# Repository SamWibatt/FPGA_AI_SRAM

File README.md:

# FPGA_AI_SRAM
Preliminary part of AI acceleration with FPGAs, interfacing external memory for greater capacity.

Memory chips I will use for the experiments are the [Cypress Semiconductor Corp. CY62157EV30LL-45ZXIT 1Mx8 SRAM (pdf)](https://www.cypress.com/file/43021/download) and the [Cypress Semiconductor Corp S29AL008J55TFNR10 1Mx8 Flash (pdf)](https://www.cypress.com/file/216396/download). 

Chose these for cost and simplicity. They have the same footprint. The Flash has the advantages of costing $0.60 in 10-quantity from Digi-Key, so being good for TSOP soldering practice, as well as being able to retain data while unpowered. The SRAM is pricier at $2.93 in single quantity, so not bad. (On edit: that's a fluke, because the chips don't have a warranty... do they work? I don't know. I just ordered 10 more in hopes that they do. I reckon sooner or later I will just need to use DRAM. **FOR LATER REFERENCE WRT DRAM** [Lattice has a project related to it](http://www.latticesemi.com/en/Products/DesignSoftwareAndIP/IntellectualProperty/ReferenceDesigns/ReferenceDesigns01/FastPageModeDRAMController) though that appears to be just with one kind. Find docs about it in general; writing an sdram controller might not be so scary and looks like a good intermediate project. Perhaps https://pdfs.semanticscholar.org/d960/f5cc9782719dcfa780b4f4aea51b8f791c62.pdf, and let's move this discussion to a new project or at least the wiki.)

Their interface is easy to understand and they're kind of OK for speed. Speed in actual wall time is not the point of this exercise so much as speed in terms of clock cycles; I'm looking more for savings of complexity which will translated to savings in time once it can run on "real" hardware.

# Objective

The initial goal is to try accelerating some data structures such as red/black trees and running some old AI techniques like A* to get a feel for how well programmable logic can tighten them up.

Ultimately, I want to implement modern methods such as RNNs, but since I'm still working on tiny cheap eval boards it's unlikely I can do much - but I will look into it, and I will learn some useful things in this endeavor that will transfer (transfer learning LOL) I imagine I'm also going to have to pick up DSP for best results there.

OK so now got this project cloned onto makevm4, let's try a push from it. Not on the VPN, so I expect it to work.

Copied over some initial stuff like osresearch's makefile for their serial project, need hack up to do what I want AND DO WHATEVER I NEED TO DO TO SATISFY THE TERMS OF THEIR LICENSE!!!!!!!!!!!!

# Notes

**Release / tag v0.1 should be a good skeleton for future icestorm projects** But [the repository VerilogSkeleton](https://github.com/SamWibatt/VerilogSkeleton) should also be that and I will maintain it as such.

I will be keeping my usual stream of consciousness [notes in the repo wiki, qv](https://github.com/SamWibatt/FPGA_AI_SRAM/wiki).

Makefile, Makefile.icestorm, and upduino_v2.pcf are copied and modified from osresearch's code at https://github.com/osresearch/up5k licensed under GPL3

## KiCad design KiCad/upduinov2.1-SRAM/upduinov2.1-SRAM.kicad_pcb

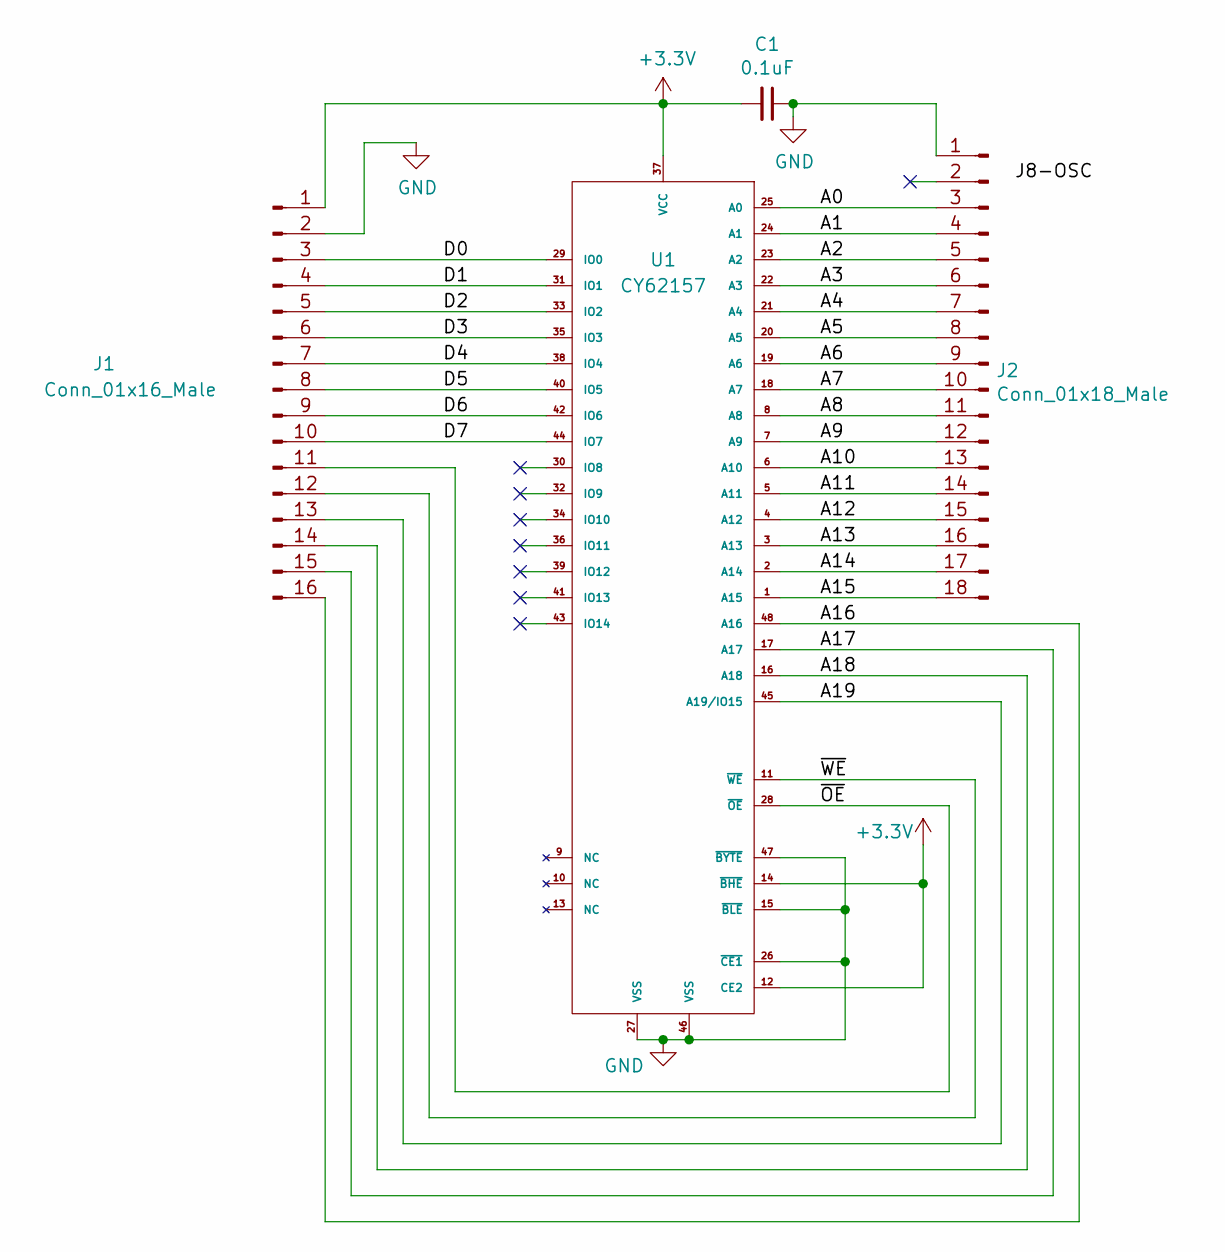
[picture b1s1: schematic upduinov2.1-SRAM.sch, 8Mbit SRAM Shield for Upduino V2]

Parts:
C1: 0.1uF; C_0805_2012Metric
J1: Conn_01x16_Male; PinHeader_1x16_P2.54mm_Vertical
J2: Conn_01x18_Male; PinHeader_1x18_P2.54mm_Vertical
U1: CY62157; TSOP-I-48_18.4x12mm_P0.5mm

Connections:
+3V3: C1.2, J1.1, U1.12 (CE2), U1.14 (~BHE), U1.37 (VCC)
/A0: J2.3, U1.25 (A0)
/A1: J2.4, U1.24 (A1)
/A2: J2.5, U1.23 (A2)
/A3: J2.6, U1.22 (A3)
/A4: J2.7, U1.21 (A4)
/A5: J2.8, U1.20 (A5)
/A6: J2.9, U1.19 (A6)
/A7: J2.10, U1.18 (A7)
/A8: J2.11, U1.8 (A8)
/A9: J2.12, U1.7 (A9)
/A10: J2.13, U1.6 (A10)
/A11: J2.14, U1.5 (A11)
/A12: J2.15, U1.4 (A12)
/A13: J2.16, U1.3 (A13)
/A14: J2.17, U1.2 (A14)
/A15: J2.18, U1.1 (A15)
/A16: J1.16, U1.48 (A16)
/A17: J1.15, U1.17 (A17)
/A18: J1.14, U1.16 (A18)
/A19: J1.13, U1.45 (A19/IO15)
/D0: J1.3, U1.29 (IO0)
/D1: J1.4, U1.31 (IO1)
/D2: J1.5, U1.33 (IO2)
/D3: J1.6, U1.35 (IO3)
/D4: J1.7, U1.38 (IO4)
/D5: J1.8, U1.40 (IO5)
/D6: J1.9, U1.42 (IO6)
/D7: J1.10, U1.44 (IO7)
/~OE: J1.11, U1.28 (~OE)
/~WE: J1.12, U1.11 (~WE)
GND: C1.1, J1.2, J2.1, U1.15 (~BLE), U1.26 (~CE1), U1.27 (VSS), U1.46 (VSS), U1.47 (~BYTE)

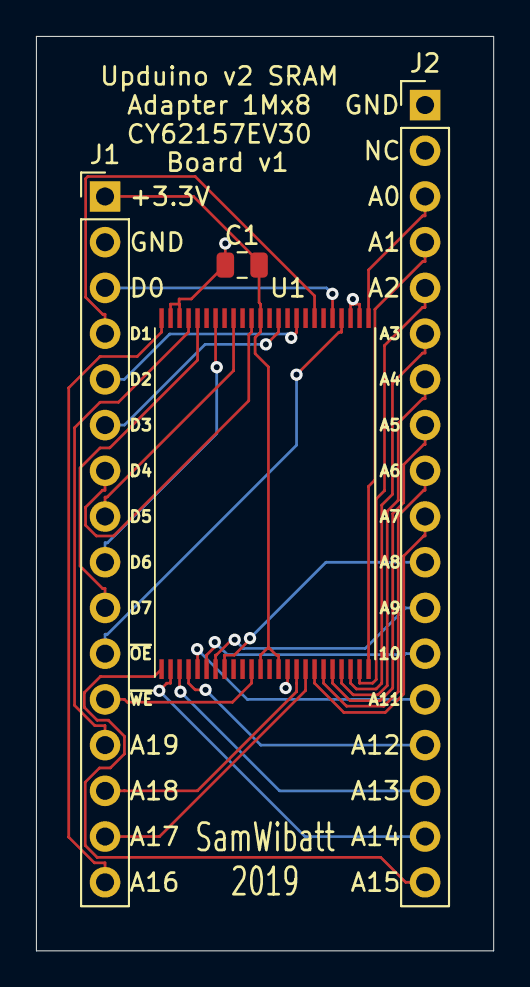
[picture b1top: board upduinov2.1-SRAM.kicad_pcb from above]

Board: 2 copper layers, 25.4 x 50.8 mm, 4 parts (0 on the bottom side), 32 nets.

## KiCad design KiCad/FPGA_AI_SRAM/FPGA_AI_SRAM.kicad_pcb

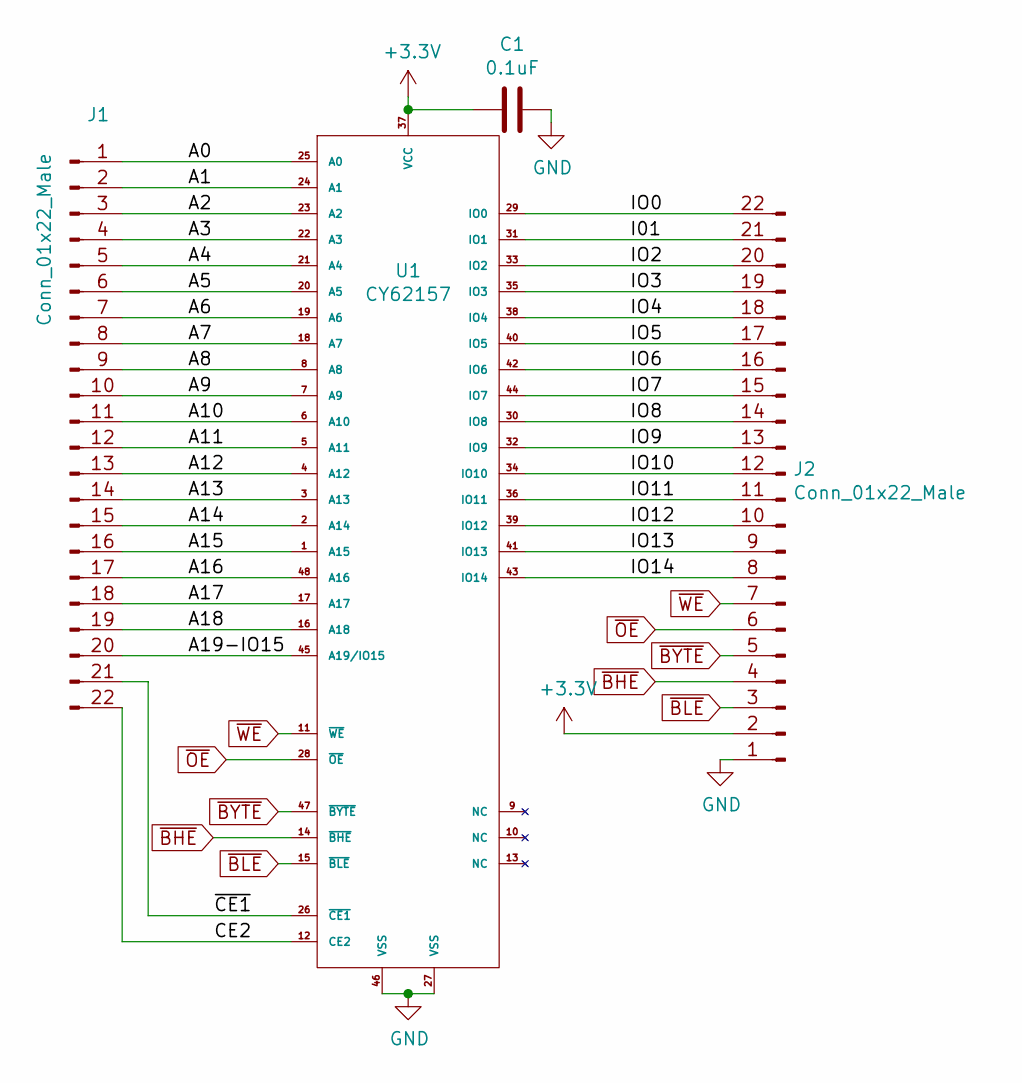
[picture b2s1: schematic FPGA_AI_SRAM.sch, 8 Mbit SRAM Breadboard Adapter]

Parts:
C1: 0.1uF; C_0805_2012Metric
J1, J2: Conn_01x22_Male; PinHeader_1x22_P2.54mm_Vertical
U1: CY62157; TSOP-I-48_18.4x12mm_P0.5mm

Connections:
+3V3: C1.2, J2.2, U1.37 (VCC)
/A0: J1.1, U1.25 (A0)
/A1: J1.2, U1.24 (A1)
/A2: J1.3, U1.23 (A2)
/A3: J1.4, U1.22 (A3)
/A4: J1.5, U1.21 (A4)
/A5: J1.6, U1.20 (A5)
/A6: J1.7, U1.19 (A6)
/A7: J1.8, U1.18 (A7)
/A8: J1.9, U1.8 (A8)
/A9: J1.10, U1.7 (A9)
/A10: J1.11, U1.6 (A10)
/A11: J1.12, U1.5 (A11)
/A12: J1.13, U1.4 (A12)
/A13: J1.14, U1.3 (A13)
/A14: J1.15, U1.2 (A14)
/A15: J1.16, U1.1 (A15)
/A16: J1.17, U1.48 (A16)
/A17: J1.18, U1.17 (A17)
/A18: J1.19, U1.16 (A18)
/A19-IO15: J1.20, U1.45 (A19/IO15)
/CE2: J1.22, U1.12 (CE2)
/I01: J2.21, U1.31 (IO1)
/IO0: J2.22, U1.29 (IO0)
/IO2: J2.20, U1.33 (IO2)
/IO3: J2.19, U1.35 (IO3)
/IO4: J2.18, U1.38 (IO4)
/IO5: J2.17, U1.40 (IO5)
/IO6: J2.16, U1.42 (IO6)
/IO7: J2.15, U1.44 (IO7)
/IO8: J2.14, U1.30 (IO8)
/IO9: J2.13, U1.32 (IO9)
/IO10: J2.12, U1.34 (IO10)
/IO11: J2.11, U1.36 (IO11)
/IO12: J2.10, U1.39 (IO12)
/IO13: J2.9, U1.41 (IO13)
/IO14: J2.8, U1.43 (IO14)
/~CE1: J1.21, U1.26 (~CE1)
GND: C1.1, J2.1, U1.27 (VSS), U1.46 (VSS)
~BHE: J2.4, U1.14 (~BHE)
~BLE: J2.3, U1.15 (~BLE)
~BYTE: J2.5, U1.47 (~BYTE)
~OE: J2.6, U1.28 (~OE)
~WE: J2.7, U1.11 (~WE)

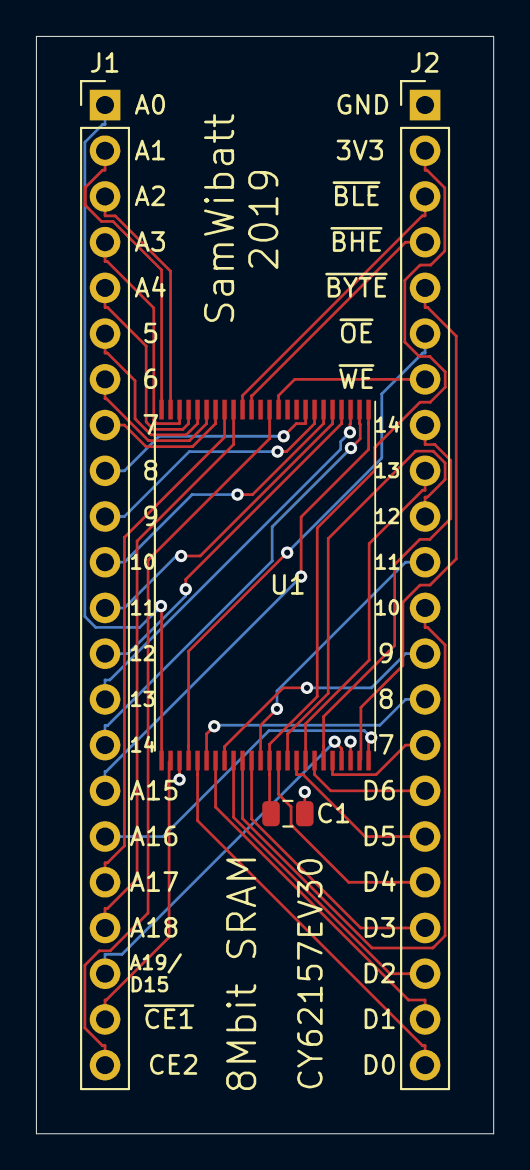
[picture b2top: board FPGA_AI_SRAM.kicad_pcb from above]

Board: 2 copper layers, 25.4 x 61.0 mm, 4 parts (0 on the bottom side), 44 nets.

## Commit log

2019-11-21 1st buildable, blinky, not-bad skeleton
2019-11-22 make test almost works, needs make clean first
2019-11-22 skeleton basically works but icky
2019-11-23 make test creates err and out files
2019-11-23 Makefile works with .v dependency lists
2019-11-24 makefile now good! do a release
2019-11-24 sync
2019-12-07 added KiCad project and sram part
2019-12-07 kicad template for OSH Park hopework
2019-12-07 paddle schematic done
2019-12-08 possible pcb v1
2019-12-08 better board with hand routed decoupler
2019-12-08 better board fully autorouted
2019-12-08 improved silkscreen, added 3d img
2019-12-08 3d back view added
2019-12-08 added net names
2019-12-09 added blank upduino kicad
2019-12-09 made upduinov2.1-sram kicad project w oshpark settings
2019-12-09 fixed pin number on upd-SRAM pcb
2019-12-10 New Upduino shield
2019-12-10 updv2 pcb v1 w handroute decoupler
2019-12-10 cropped pcb img
2019-12-11 added board version number
2020-01-13 sram module stubbed, test doesn't compile
2020-01-13 stub ram test compiles
2020-02-09 first version of timing calc script
2020-02-14 first cut at config includes
2020-02-15 added .inc includes to sram.v
2020-02-15 progress on state machine yay
2020-02-16 put wishbone signals on sram.v, mad broken but gotta catch a plane
2020-02-23 sram n top_test are using wishbone signals, still a mess
2020-02-23 strobe logic v1
2020-02-23 added clock starting constants for modes in sram_config.py
2020-02-23 sram state machine refactor
2020-02-24 sram_config.py emits counter values
2020-02-25 starting use of timing constants
2020-02-27 further state machine
2020-02-28 starting cycle logic
2020-02-29 strobe waits for ack
2020-03-01 added cycle tags and error state
2020-03-06 block read roughed
